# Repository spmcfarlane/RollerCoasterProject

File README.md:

# RollerCoasterProject
Sensor array arduino shield for roller coaster cart/RC applications

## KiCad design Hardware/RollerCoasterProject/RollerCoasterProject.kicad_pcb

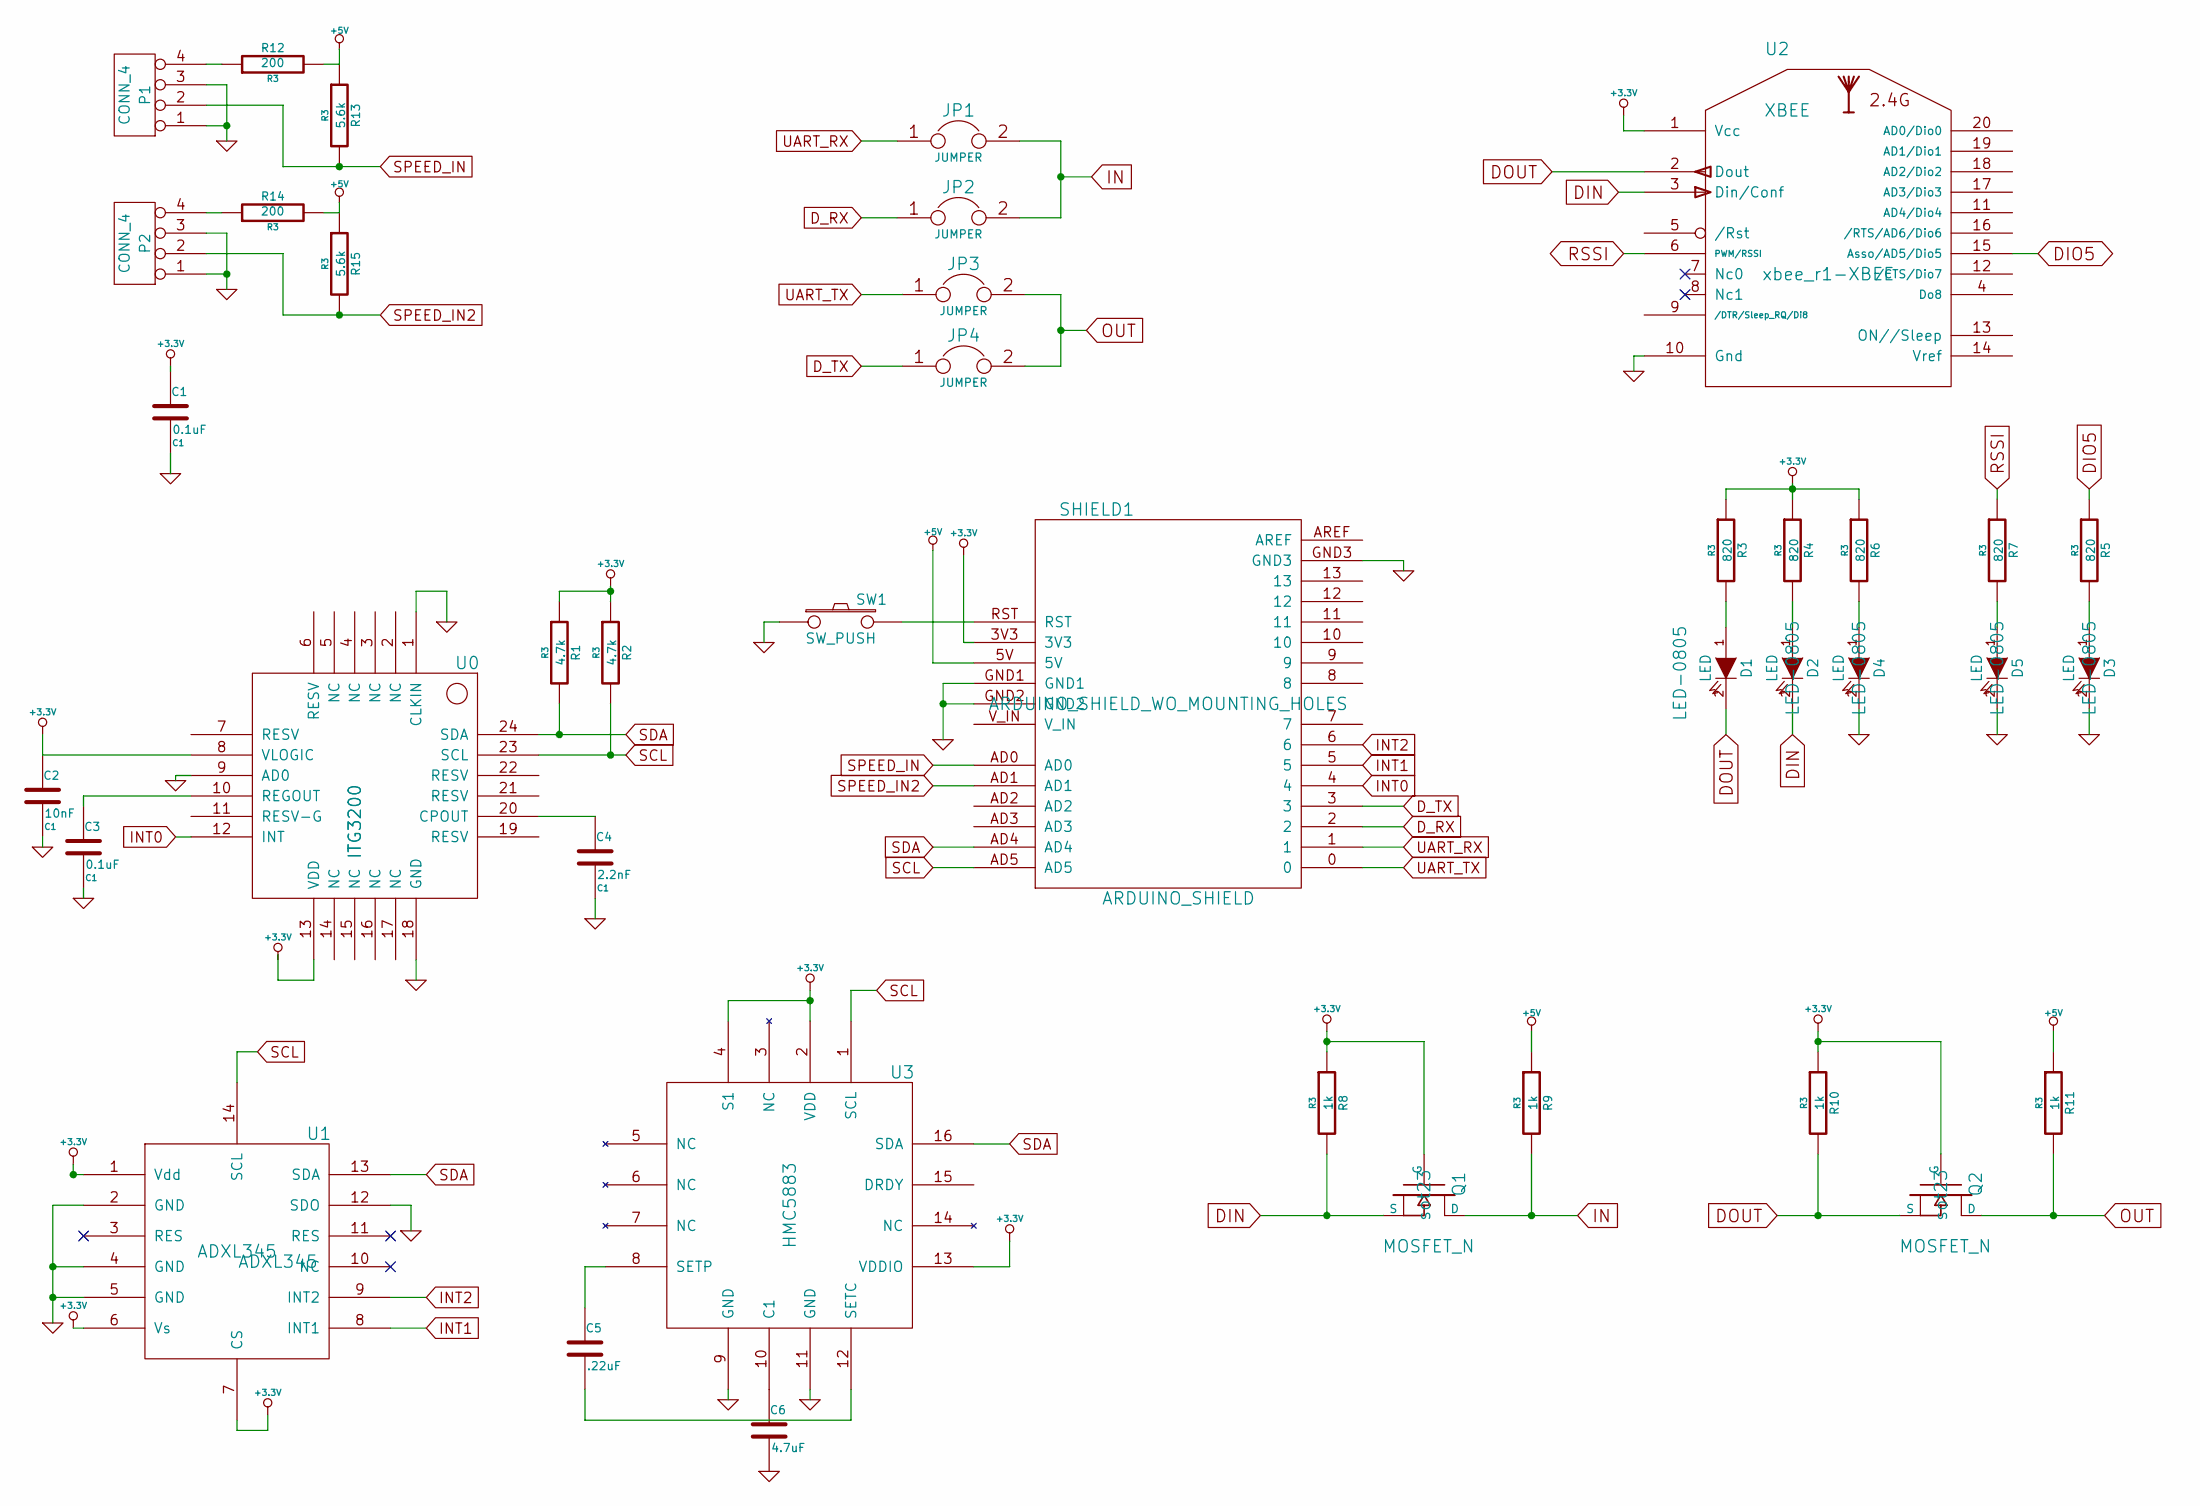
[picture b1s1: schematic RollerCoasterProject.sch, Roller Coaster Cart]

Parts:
C1, C3: 0.1uF; C1
C2: 10nF; C1
C4: 2.2nF; C1
C5: .22uF
C6: 4.7uF
D1, D2, D3, D4, D5: LED; LED-0805
JP1, JP2, JP3, JP4: JUMPER
P1, P2: CONN_4
Q1, Q2: MOSFET_N; sot23
R1, R2: 4.7k; R3
R3, R4, R5, R6, R7: 820; R3
R8, R9, R10, R11: 1k; R3
R12, R14: 200; R3
R13, R15: 5.6k; R3
SHIELD1: ARDUINO_SHIELD; ARDUINO_SHIELD_WO_MOUNTING_HOLES
SW1: SW_PUSH
U0: ITG3200
U1: ADXL345
U2: XBEE; xbee_r1-XBEE
U3: HMC5883

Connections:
+3.3V: C1.1, C2.1, Q1.1 (G), Q2.1 (G), R1.1, R2.1, R3.1, R4.1, R6.1, R8.1, R10.1, SHIELD1.3V3, U0.8 (VLOGIC), U0.13 (VDD), U1.1 (Vdd), U1.6 (Vs), U1.7 (CS), U2.1 (Vcc), U3.2 (VDD), U3.4 (S1), U3.13 (VDDIO)
+5V: R9.1, R11.1, R12.2, R13.1, R14.2, R15.1, SHIELD1.5V
DIN: D2.2 (K), Q1.3 (S), R8.2, U2.3 (Din/Conf)
DIO5: R5.1, U2.15 (Asso/AD5/Dio5)
DOUT: D1.2 (K), Q2.3 (S), R10.2, U2.2 (Dout)
D_RX: JP2.1, SHIELD1.2
D_TX: JP4.1, SHIELD1.3
GND: C1.2, C2.2, C3.2, C4.2, C6.2, D3.2 (K), D4.2 (K), D5.2 (K), P1.1, P1.3, P2.1, P2.3, SHIELD1.GND1, SHIELD1.GND2, SHIELD1.GND3, SW1.1, U0.1 (CLKIN), U0.9 (AD0), U0.18 (GND), U1.2 (GND), U1.4 (GND), U1.5 (GND), U1.12 (SDO), U2.10 (Gnd), U3.9 (GND), U3.11 (GND)
IN: JP1.2, JP2.2, Q1.2 (D), R9.2
INT0: SHIELD1.4, U0.12 (INT)
INT1: SHIELD1.5, U1.8 (INT1)
INT2: SHIELD1.6, U1.9 (INT2)
unnamed: P1.4, R12.1
unnamed: P2.4, R14.1
unnamed: C4.1, U0.20 (CPOUT)
unnamed: C3.1, U0.10 (REGOUT)
unnamed: C6.1, U3.10 (C1)
unnamed: C5.2, U3.12 (SETC)
unnamed: C5.1, U3.8 (SETP)
unnamed: SHIELD1.RST, SW1.2
unnamed: D5.1 (A), R7.2
unnamed: D4.1 (A), R6.2
unnamed: D3.1 (A), R5.2
unnamed: D2.1 (A), R4.2
unnamed: D1.1 (A), R3.2
OUT: JP3.2, JP4.2, Q2.2 (D), R11.2
RSSI: R7.1, U2.6 (PWM/RSSI)
SCL: R2.2, SHIELD1.AD5, U0.23 (SCL), U1.14 (SCL), U3.1 (SCL)
SDA: R1.2, SHIELD1.AD4, U0.24 (SDA), U1.13 (SDA), U3.16 (SDA)
SPEED_IN: P1.2, R13.2, SHIELD1.AD0
SPEED_IN2: P2.2, R15.2, SHIELD1.AD1
UART_RX: JP1.1, SHIELD1.1
UART_TX: JP3.1, SHIELD1.0

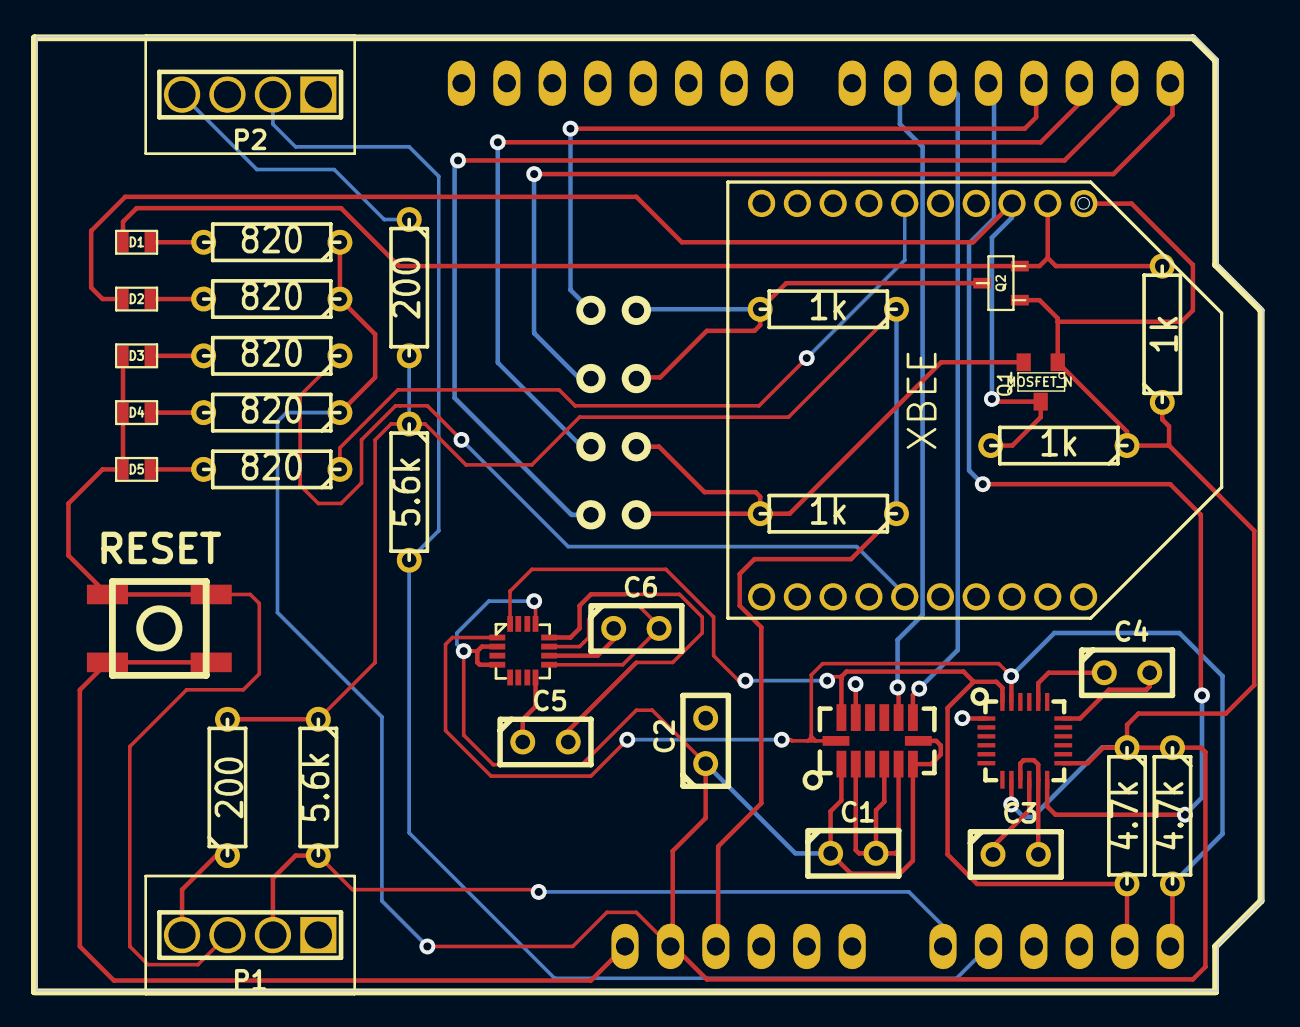
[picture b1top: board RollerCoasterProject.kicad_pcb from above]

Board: 2 copper layers, 68.6 x 53.3 mm, 40 parts (0 on the bottom side), 33 nets.

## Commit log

2017-01-29 Initial Commit
    Initial commit of all software and hardware design files
2017-06-17 Added IST8310 to the FreeSixIMU
2020-04-20 Add files via upload
    Added mag test to repo. This was a succcessful test of the IST8310 on RollerCoasterProject PCB
2020-04-26 Added test commit comments to magtest
2020-05-18 Fixed an error with the IST library where it used the boolean OR function instead of the bitwise or function
2020-05-18 Removing redundant lines from IST8310 library
2020-05-31 Added SD card recording
